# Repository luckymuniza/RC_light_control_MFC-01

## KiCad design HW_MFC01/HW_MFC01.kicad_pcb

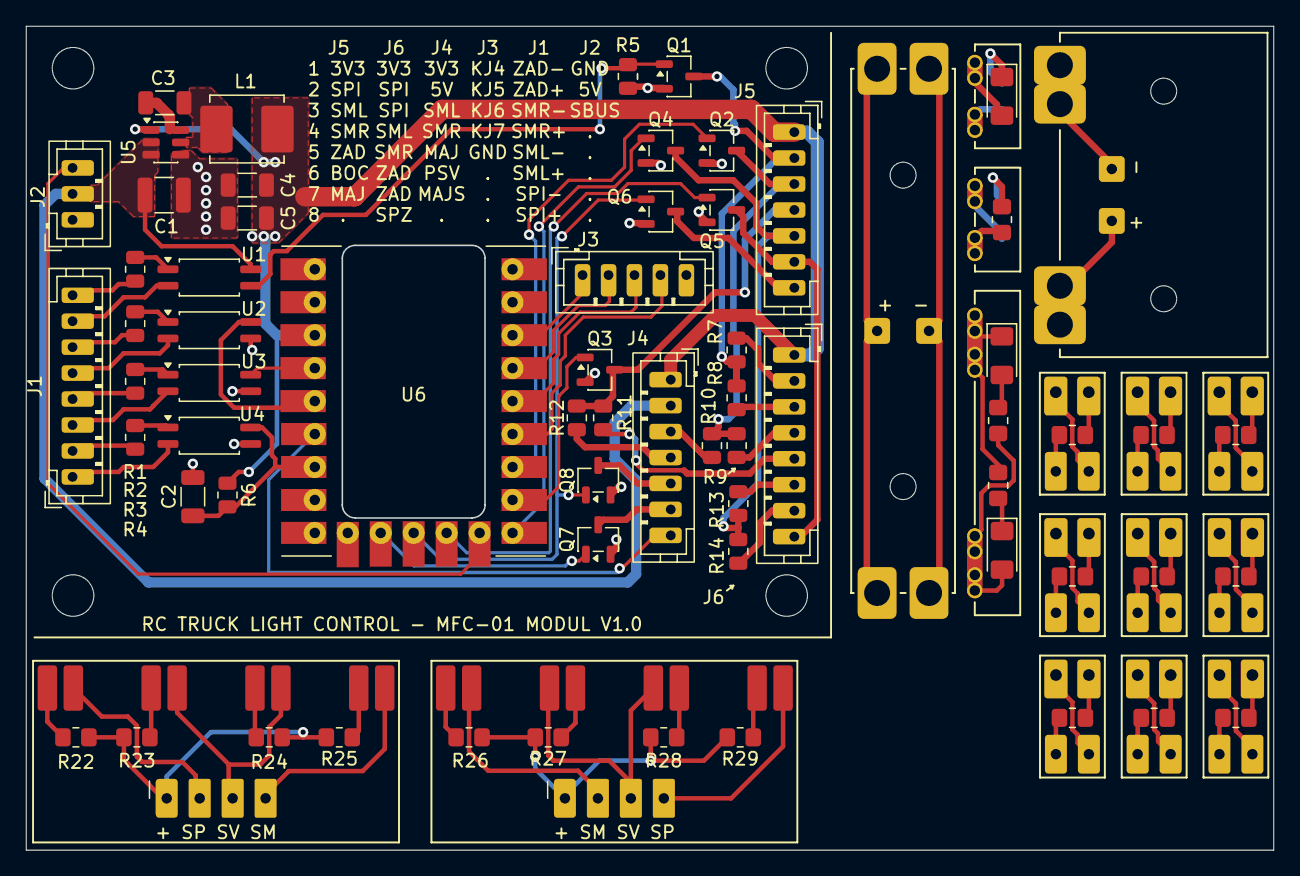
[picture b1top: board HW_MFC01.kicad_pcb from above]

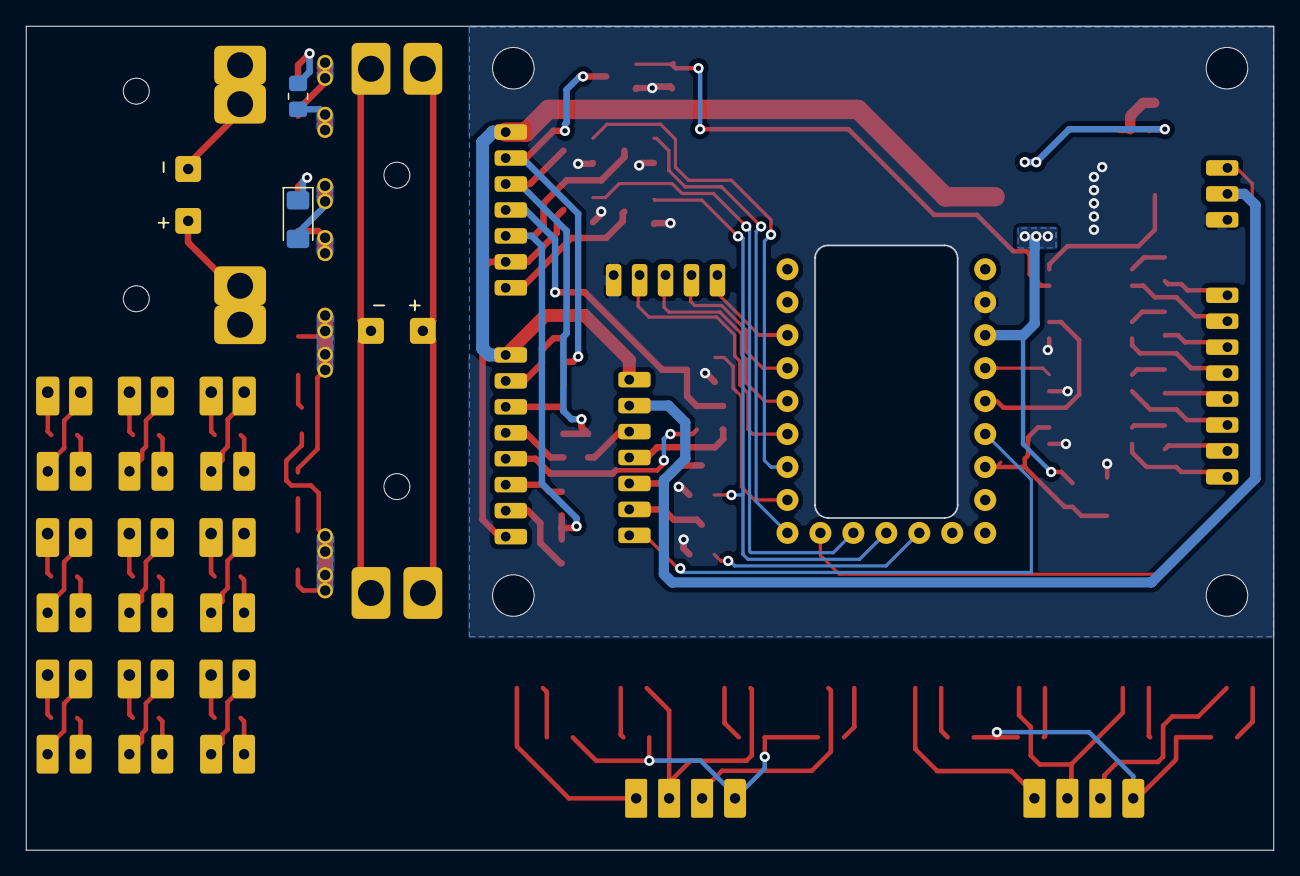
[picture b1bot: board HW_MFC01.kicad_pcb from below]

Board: 2 copper layers, 96.1 x 63.5 mm, 96 parts (2 on the bottom side), 88 nets.

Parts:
C1: 10u/50V; C_1210_3225Metric
C2, C3: 100n; C_1206_3216Metric
C4, C5: 22u/16V; C_1206_3216Metric
D1, D2, D3, D4: LED; LED_1206_3216Metric_Pad1.42x1.75mm_HandSolder
D5, D5#2, D5#3, D6, D6#2, D6#3, D7, D7#2, D7#3: LED; LED_D3.0mm_mod
H1, H2, H3, H4: MountingHole; MountingHole_3.2mm_M3
J1, J6: Conn_01x08; JST_PH_B8B-PH-K_1x08_P2.00mm_Vertical_Bigpads
J2: JST_PH_B3B-PH-K_1x03_P2.00mm_Vertical_Bigpads
J3: Conn_01x05; JST_PH_B5B-PH-K_1x05_P2.00mm_Vertical_Bigpads
J4, J5: Conn_01x07; JST_PH_B7B-PH-K_1x07_P2.00mm_Vertical_Bigpads
J7: Conn_01x06_Pin; REAR_SPZ1
J8, J9: Conn_01x02_Pin; REAR_SPZ2
J10: Conn_01x04_Pin; REAR2_SPZ1
J11: Conn_01x02_Pin; REAR2_SPZ2
J12, J12#2, J12#3, J13, J13#2, J13#3, J14, J14#2, J14#3: Conn_01x02_Pin; PinSocket_1x02_P2.54mm_modpads
J15, J18: Conn_01x08; rearlight_PCB
J19, J20: Conn_01x04_Pin; PinSocket_1x04_P2.54mm_modpads
L1: 6.8uH; L_Panasonic_PCC-M0530M
Q1, Q2, Q3, Q4, Q5, Q6, Q7, Q8: IRLML0030; SOT-23-3
R1, R2, R3, R4, R5, R6, R7, R8, R9, R10, R11, R12, R13, R14: 10k; R_0805_2012Metric
R15, R16, R17, R18, R19, R19#2, R19#3, R20, R20#2, R20#3, R21, R21#2, R21#3, R22, R23, R24, R25, R26, R27, R28, R29: R; R_0805_2012Metric_Pad1.20x1.40mm_HandSolder
U1, U2, U3, U4: EL3H7; SOP-4_4.4x2.6mm_P1.27mm
U5: AP63203WU; TSOT-23-6
U6: RP2040-Zero; RP2040 Zero undercutted

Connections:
+3.3V: C4.1, C5.1, J4.1, J5.1, J6.1, L1.2, R6.1, U5.1 (FB), U6.3 (3V3)
+5V: C1.1, J2.2, J4.2, U1.4, U5.2 (EN), U5.3 (IN)
/BEACON F: J4.5, Q8.3 (D)
/BEACON_OUT: Q6.1 (G), Q8.1 (G), U6.21 (GP11)
/FRONT_BEACON_PWM: J4.7, U6.6 (GP27)
/HEAD LIGHTS: J4.6, Q7.3 (D)
/HEAD_LIGHTS: Q7.1 (G), U6.20 (GP12)
/J4: J3.1, U6.12 (GP2)
/J5: J3.2, U6.13 (GP3)
/J6: J3.3, U6.14 (GP4)
/J7: J3.4, U6.15 (GP5)
/REAR L: J6.6, R13.1
/REAR R: J6.7, R14.1
/REAR+: J1.2, R4.1
/REAR-: J1.1, U4.2
/REAR_LIGHT_IN: C2.1, R6.2, U4.4, U6.7 (GP26)
/REAR_PWM_OUT: Q4.1 (G), U6.18 (GP8)
/REV+: J1.8, R1.1
/REV-: J1.7, U1.2
/REVERSE L: J6.2, R7.1
/REVERSE R: J6.3, R8.1
/REVERSE_LIGHTS_IN: Q1.1 (G), R5.2, U1.3
/SBUS_IN: J2.3, U6.23 (GP9)
/SIDE_LIGHTS: Q5.1 (G), U6.22 (GP10)
/TRA BEACON: J5.7, Q6.3 (D)
/TRA REAR: J5.5, Q4.3 (D), R13.2, R14.2
/TRA REVERSE: J5.2, Q1.3 (D), R7.2, R8.2
/TRA SIDE LIGHTS/SPZ: J5.6, J6.8, Q5.3 (D)
/TRA TURN L: J5.3, Q2.3 (D), R9.2, R10.2
/TRA TURN R: J5.4, Q3.3 (D), R11.2, R12.2
/TURN F L: J4.3, R10.1
/TURN F R: J4.4, R12.1
/TURN L: J6.4, R9.1
/TURN R: J6.5, R11.1
/TURNL+: J1.6, R2.1
/TURNL-: J1.5, U2.2
/TURNR+: J1.4, R3.1
/TURNR-: J1.3, U3.2
/TURN_L_IN: U2.4, U6.5 (GP28)
/TURN_L_PWM_OUT: Q2.1 (G), U6.16 (GP6)
/TURN_R_IN: U3.4, U6.4 (GP29)
/TURN_R_PWM_OUT: Q3.1 (G), U6.17 (GP7)
GND: C1.2, C2.2, C4.2, C5.2, J2.1, J3.5, Q1.2 (S), Q2.2 (S), Q3.2 (S), Q4.2 (S), Q5.2 (S), Q6.2 (S), Q7.2 (S), Q8.2 (S), R5.1, U2.3, U3.3, U4.3, U5.4 (GND), U6.2 (GND)
unnamed: D1.2 (A), J8.1
unnamed: D1.1 (K), R15.2
unnamed: D2.2 (A), J9.1
unnamed: D2.1 (K), R16.2
unnamed: D3.2 (A), R17.2
unnamed: D3.1 (K), J11.1, R18.1
unnamed: D4.2 (A), J11.2, R17.1
unnamed: D4.1 (K), R18.2
unnamed: D5.2 (A), D5#2.2 (A), D5#3.2 (A), J12.1, J12#2.1, J12#3.1
unnamed: D5.1 (K), D5#2.1 (K), D5#3.1 (K), R19.2, R19#2.2, R19#3.2
unnamed: D6.2 (A), D6#2.2 (A), D6#3.2 (A), J13.1, J13#2.1, J13#3.1
unnamed: D6.1 (K), D6#2.1 (K), D6#3.1 (K), R20.2, R20#2.2, R20#3.2
unnamed: D7.2 (A), D7#2.2 (A), D7#3.2 (A), J14.1, J14#2.1, J14#3.1
unnamed: D7.1 (K), D7#2.1 (K), D7#3.1 (K), R21.2, R21#2.2, R21#3.2
unnamed: J7.1, J7.3, J7.5
unnamed: J7.2, J7.4, J7.6
unnamed: J8.2, R15.1
unnamed: J9.2, R16.1
unnamed: J10.1, J10.3
unnamed: J10.2, J10.4
unnamed: J12.2, J12#2.2, J12#3.2, R19.1, R19#2.1, R19#3.1
unnamed: J13.2, J13#2.2, J13#3.2, R20.1, R20#2.1, R20#3.1
unnamed: J14.2, J14#2.2, J14#3.2, R21.1, R21#2.1, R21#3.1
unnamed: J15.1, R22.1
unnamed: J15.2, J19.2
unnamed: J15.3, R23.1
unnamed: J15.4, J15.6, J19.3
unnamed: J15.5, R24.1
unnamed: J15.7, R25.1
unnamed: J15.8, J19.4
unnamed: J18.1, R26.1
unnamed: J18.2, J20.2
unnamed: J18.3, J18.5, J20.3
unnamed: J18.4, R27.1
unnamed: J18.6, R28.1
unnamed: J18.7, R29.1
unnamed: J18.8, J20.4
unnamed: J19.1, R22.2, R23.2, R24.2, R25.2
unnamed: J20.1, R26.2, R27.2, R28.2, R29.2
unnamed: R1.2, U1.1
unnamed: R2.2, U2.1
unnamed: R3.2, U3.1
unnamed: R4.2, U4.1
unnamed: C3.2, U5.6 (BST)
unnamed: C3.1, L1.1, U5.5 (SW)
